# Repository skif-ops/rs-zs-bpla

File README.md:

# Дионея / РС ЗС-БПЛА — EVT-PRE-20

Эта ветка содержит инженерную базу одного управляемого предсерийного лота
`EVT-20`. Актуальная программа закупки — два отдельных набора по 20 станций и
один стендовый образец, всего 41 станция. Закупочная выдача имеет два явно
разделённых варианта: 21 станция (один EVT-20 плюс стендовая) и 41 станция
(два EVT-20 плюс стендовая). Расчёты для 4 и 10 станций сохранены для
сравнения, но не являются разрешением закупки.

## Зафиксированный baseline

- производственная единица управления: `EVT-20`, 20 изделий;
- программа: `2 × EVT-20 + 1 bench`, 41 станция;
- варианты закупки: `21 = EVT-20 + bench` и `41 = 2 × EVT-20 + bench`;
- резервы: два независимых EVT-20 пула; стендовый образец не создаёт третий;
- серийные номера: первый лот `DIO-EVT-001…020`, второй `DIO-EVT-021…040`,
  стендовый образец `DIO-EVT-B01`; индивидуальные travellers заполняются до
  начала сборки;
- собственная PCB станции, без отладочной платы WeAct в составе изделия;
- вычислительная платформа: `STM32U585VIT6Q`, `LQFP100_14x14`;
- четыре одинаковых микрофона, схема 3+1, база 120 мм, верхний микрофон +150 мм;
- LiFePO4 12.8 В / 40 А·ч и солнечная панель 80 Вт по точным MPN baseline;
- GSM/LTE через исходящее MQTT/TLS, резерв HTTPS/TLS, два nano-SIM в режиме
  Dual SIM Single Standby и только `public APN` в пилоте;
- LoRa `RU868` на каждом изделии; будущий `EU868` профиль в пилот не прошивается;
- BLE используется для локальной настройки, диагностики и безопасного обновления;
- корпус первого EVT-20 лота — вакуумное литьё; 3D-печать остаётся управляемым
  резервом, а ТПА — только комплектом исходных данных;
- сервер — «Мухоед» для Windows 11 и Ubuntu 24.04; Android ведётся отдельным треком.

## Текущий статус

Общий статус аппаратного выпуска: `BLOCKED / EVT NOT RUN`. Наличие документов и
успешные структурные проверки не являются завершённым аппаратным EVT.

| Область | Принято | Остаётся открытым |
|---|---|---|
| PCB-MAIN | 8L COMPLETE-105 Rev.B; `JLC08161H-3313`; 5969 route segments; 251 components; KiCad DRC 0 errors / 0 unconnected | selected-stack impedance/return-path review, POFV confirmation, Altium antenna-warning disposition, checkout DFM, Review B |
| PCB-PWR | `DIM-003` `18/18`; 90×60×1.6 mm; H1-H4 M3 NPTH; `JLC04161H-3313A`; 70/35 µm copper; ≥18 µm hole wall; расчётная силовая геометрия; точный ECO-002 применён, 14 принятых сегментов; application gate PASS | input-protection qualification, оставшаяся трассировка, rail-drop/load-step/fault/+70 °C evidence, DRC, CAM, checkout DFM, Review B |
| PCB-MIC | copper subgate и стандартный двухслойный/PCBA процесс; 9/9 engineering closures | first-panel bore/acoustic inspection, CAM comparison, общий Review B и physical EVT |
| Жгуты | 38 проводников; точные wire MPN; длины `275/440/330 mm` с 10% запасом; 16/16 engineering closures | first-off crimp height/pull, 100% continuity/polarity/cross-short/resistance, installed-route SI/thermal/cold/strain EVT |
| BOM | QG-1 PASS; technical QG-2 PASS; per-lot 4/10/20 и aggregate 41-station procurement plan | коммерческий заказ и hardware manufacturing release |
| Внешние ответы | бывшие wait gates закрыты `85/85` инженерным EVT baseline | factory e-mail не требуется; реальные checkout parser/DFM ошибки останавливают заказ и идут через ECO |

Закрытия в response-регистрах принадлежат проектной инженерии по решению
заказчика и не выдаются за ответы фабрик. Стандартные процессы приняты только для
тестовой EVT-программы; при переходе в серию повторяются supplier/site, tooling,
DFM и process qualification.

PCB-PWR `VBAT_RAW` routing 003 и `REV_GATE` routing 004 применены и прошли
точные application gates. Точный `PCB-PWR-BUCK-POWER-STAGE-ECO-002` теперь
применён к authoritative board; активная плата содержит 14 принятых сегментов,
ноль vias и ноль zones. Commit-bound application gate прошёл CI #692,
PCB-PWR Schematic #103 и PCB Native #357. Физический first-article +70 °C,
оставшаяся трассировка и все выпускные гейты открыты.

Серверная часть включает обновлённую обработку подтверждённого класса «лютый» в
трёх проверенных аудиосценариях «Мухоеда»; это программное изменение не закрывает
аппаратные гейты.

## Контроль выпуска

Каждый поставочный объект проходит два последовательных контроля:

1. `QG-1 Completeness` — наличие, версия, взаимные ссылки и контрольная сумма.
2. `QG-2 Technical` — ERC/DRC, сборка, тест, визуальная проверка или измерение.

Основные команды:

```bash
python tools/validate_evt_pre_20_bom_qg1.py
python tools/audit_evt_pre_20_bom_qg2.py --strict
python tools/audit_evt_engineering_manufacturing_baseline_rev_a.py
python tools/audit_evt_pre_20_hardware_release.py
python tools/kicad_native_gate.py
```

Gerber, прошивки, бинарники, корпуса и серверный релиз не считаются выпущенными,
пока их собственные гейты не имеют требуемые evidence. Hardware-only gate не
блокируется Android/server/обычным firmware, кроме явных аппаратных зависимостей.

## Навигация

- [`BRANCH_SCOPE.md`](BRANCH_SCOPE.md) — границы ветки и актуальный срез.
- [`config/EVT_PRE_20_BASELINE.yaml`](config/EVT_PRE_20_BASELINE.yaml) — машинно-читаемая конфигурация.
- [`docs/DELIVERABLE_REGISTER_EVT_PRE_20.csv`](docs/DELIVERABLE_REGISTER_EVT_PRE_20.csv) — реестр поставки и gates.
- [`docs/OPEN_INPUTS_FOR_FREEZE.csv`](docs/OPEN_INPUTS_FOR_FREEZE.csv) — входные данные, блокирующие финальный выпуск.
- [`docs/EVT_PRE_20_LONG_RANGE_ACOUSTIC_HEAD_TRADE_STUDY_REV_C.pdf`](docs/EVT_PRE_20_LONG_RANGE_ACOUSTIC_HEAD_TRADE_STUDY_REV_C.pdf) — актуальный двуязычный управляемый выпуск исследования дальнего акустического тракта: физика распространения, классы целей, сравнение микрофонов, рупоров, отражателей и резонаторов, план прототипа LR-1. Производственный baseline плат не изменён.
- [`hardware/EVT_PRE_20_ACOUSTIC_TRADE_STUDY_REV_C.xlsx`](hardware/EVT_PRE_20_ACOUSTIC_TRADE_STUDY_REV_C.xlsx) — сводная книга вариантов, целевых классов, расчёта потерь на 2 км, матрицы физических испытаний и источников. Машиночитаемые таблицы сохранены рядом в CSV.
- [`hardware/EVT_PRE_20_BOM_POLICY_REV_A.md`](hardware/EVT_PRE_20_BOM_POLICY_REV_A.md) — BOM и количества.
- [`hardware/EVT_PROGRAM_PROCUREMENT_VARIANTS_REV_A.csv`](hardware/EVT_PROGRAM_PROCUREMENT_VARIANTS_REV_A.csv) — реестр вариантов закупки 21 и 41.
- [`hardware/EVT_PROGRAM_1X20_PLUS_1_PROCUREMENT_REV_A.csv`](hardware/EVT_PROGRAM_1X20_PLUS_1_PROCUREMENT_REV_A.csv) — вариант на 21 станцию.
- [`hardware/EVT_PROGRAM_2X20_PLUS_1_PROCUREMENT_REV_A.csv`](hardware/EVT_PROGRAM_2X20_PLUS_1_PROCUREMENT_REV_A.csv) — полный план на 41 станцию.
- [`hardware/HARDWARE_PRODUCTION_RELEASE_GATE_REV_A.md`](hardware/HARDWARE_PRODUCTION_RELEASE_GATE_REV_A.md) — hardware release gate.
- [`manufacturing/README.md`](manufacturing/README.md) — маршрут сборки, traceability и EOL.
- [`tests/EVT_MASTER_PLAN.md`](tests/EVT_MASTER_PLAN.md) — последовательность EVT.
- [`android/README.md`](android/README.md) — отдельный Android-трек.

## Наследование

Ветка создана от `evt` commit `2ec1d6dc81e3a16b7c127f1bbfe03f3945a72c45`.
Поставочные материалы `evt-mb` сюда не переносятся. Общие проверенные изменения
могут отдельно продвигаться в `develop` и `main`. Макетная плата 70×90 мм и
WeAct STM32U585CIU6 не являются производственной документацией EVT-PRE-20.

## Финальный производственный комплект REV_D7

Финальная документальная выдача для закупки и производства EVT-PRE-20 находится в
[`releases/EVT_PRE_20_REV_D7`](releases/EVT_PRE_20_REV_D7/README.md). PCB-MAIN Rev.B
зафиксирована как восьмислойная. Фабричный архив содержит Altium/CAM для PCB-MAIN,
PCB-PWR и PCB-MIC без KiCad. Физические first article, EOL и EVT заполняются после
изготовления и не отмечены как выполненные заранее.

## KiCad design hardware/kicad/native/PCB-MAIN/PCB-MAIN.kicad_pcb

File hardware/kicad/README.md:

> **CURRENT PCB-MAIN SOURCE — REV.B (2026-10-16):** `native/PCB-MAIN/PCB-MAIN.kicad_pcb` is now PCB-MAIN COMPLETE-105 Rev.B with 8 copper layers. The former 6-layer native source is preserved under `retired/PCB-MAIN-6L-REV-A-2026-10-16/`. Rev.A 6-layer routing/stack sections below are historical.

# ZS-BPLA EVT-PRE-20 KiCad package

Status: `NATIVE SOURCE CONTROLLED / NOT FOR MANUFACTURE`
Configuration: `EVT-PRE-20 Rev.A`
Authoritative branch: `evt-pre-20`

This directory is the authoritative electrical-CAD source package for the EVT-PRE-20 custom-PCB build. The three native projects and their required hierarchical child sheets are present. It remains blocked from manufacturing until each provisional board is completed and the required ERC/DRC, CAM, DFM and independent reviews are complete.

## Frozen baseline used for capture

- MCU: `STM32U585VIT6Q`, LQFP100 14x14 mm. The earlier `STM32U585CIU6`/48-pin and `STM32U585ZIT6Q` references are superseded for EVT-PRE-20.
- Microphones: 4 x TDK/InvenSense `T5838`, identical MPN; same lot preferred.
- Acoustic geometry: 3+1, equilateral base 120 mm, upper microphone +150 mm over center.
- Cellular: Quectel `BG95-M3` candidate, two physical nano-SIM slots through external 2:1 SIM mux, Dual-SIM Single-Standby only.
- GNSS/PPS: independent u-blox `MAX-M10S` class receiver.
- LoRa: Ebyte `E22-900M22S` / SX1262 class, RU868 pilot profile on every station in the selected 4, 10 or 20-unit EVT lot.
- BLE commissioning/diagnostics/OTA coprocessor: Raytac `MDBT50Q-P1MV2` based on Nordic `nRF52840`, integrated PCB antenna. `ESP32-C3-MINI-1-N4` is superseded and forbidden in active Rev.A BOM/capture.
- BLE requirements: BLE 2M/1M/Coded Long Range, authenticated commissioning, signed OTA, local diagnostics; Wi-Fi is not required.
- Local storage: W25Q512-class 64 MB NOR plus industrial microSD.
- Power source: 12.8 V LiFePO4 40-60 Ah, external 10 A LiFePO4 MPPT, 60-80 W solar panel.
- MPPT function is external. Do not reintroduce the older BQ24650/CN3791 charger topology into EVT-PRE-20 PCB-MAIN or PCB-PWR.

## PCB set

1. `PCB-MAIN`: MCU, BG95, dual SIM, MAX-M10S, LoRa module, nRF52840 BLE module, NOR, microSD, sensors, USB service, SWD and test points.
2. `PCB-MIC`: one T5838 microphone leaf; four identical boards per station.
3. `PCB-PWR`: protected battery interface and DC/DC rails for 3.8 V modem, 3.3 V digital/AON and 1.8 V microphone domains. External MPPT remains a separate assembly.

PCB-PWR `C1-C21`, `R1-R15`, `NT1-NT3` and `TP1-TP10` are bound from
`hardware/PCB_PWR_PASSIVE_AUTHORITY_REV_A.csv`. This is a capture/placement input,
not a manufacturing release; its electrical, package, fixture and environmental
blockers remain explicit in the authority.

PCB-PWR now uses a human-readable five-page native hierarchy: one system overview
plus four functional child sheets for input protection/current monitoring, 3V8,
3V3 and 1V8/harness interfaces. The controlled materializer gives every connected
pin an explicit wire stub and the independent audit proves exact pad/net
equivalence to the native PCB. The C20/C21 local-CIN_HF ECO supersedes prior
KiCad 9 ERC/PDF and human decisions for the active source; fresh commit-bound
evidence and independent human acceptance remain open.

PCB-PWR currently contains a native, unrouted placement canvas with 62 electrical
footprints plus four board-only mounting holes. `DIM-003` is accepted `18/18`
for the EVT batch: the `90 x 60 x 1.6 mm` basis, round H1-H4 NPTH pattern,
connector/fixture service volumes and conservative STEP envelope are controlled.
Routing and copper zones remain absent; serial enclosure revalidation is mandatory.
`hardware/PCB_PWR_CAPTURE_STATUS_REV_A.json` is the machine-readable release
interlock for this state.

The bounded `DIM-003` authority is controlled by
`hardware/reviews/PCB_PWR_DIM_003_REQUEST_REV_A.json`; all 18 response rows are
accepted for EVT. It freezes the EVT outline, mounting, J1/J2, DFT,
assembled-height, enclosure/thermal, harness-datum and frozen-STEP inputs without
authorizing serial mechanics or manufacture.

The bounded fitted-body clearance repack passes a strict independent subgate:
all 44 simultaneously fitted footprints have controlled courtyards, the required
minimum gap is `0.20 mm`, the observed minimum is `0.22 mm`, and conflicts are
zero. This result excludes DNP/PCB-feature service checks and does not approve
the serial enclosure and exact component 3D fit; EVT connector mating/bend
volumes, mounting, DFT fixture access and assembled envelope are accepted.
Routing and Review B remain open.

`hardware/PCB_PWR_ROUTING_AUTHORITY_REV_A.csv` classifies all 31 native nets as a
pre-route input, including high-current paths, three controlled net-tie returns,
switch/bootstrap loops, Kelvin sense, feedback and I2C. The separate
`PCB_PWR_JLC04161H_3313_EVT_ROUTING_BASIS_REV_A.json` plus the 31-row
`PCB_PWR_EVT_ROUTE_RULES_REV_A.csv` now permit a bounded engineering routing
candidate using a conservative 35 µm screen. `DIM-003` is accepted for EVT;
final copper/plating, via-current capacity, fault energy, physical thermal
evidence, routing completion and manufacture remain open.

## Logical sheet plan

1. `01_POWER` - protected input and regulated rails; no integrated solar MPPT.
2. `02_MCU` - STM32U585VIT6Q, clocks, reset, SWD, decoupling, boot straps.
3. `03_AUDIO` - four PDM channels, common clock fanout/interface, microphone connectors.
4. `04_GNSS` - MAX-M10S, TIMEPULSE/PPS, RF connector/bias, backup supply.
5. `05_CELLULAR` - BG95-M3, 3.8 V transient decoupling, 1.8 V logic translation, dual nano-SIM mux and ESD.
6. `06_LORA` - E22-900M22S/SX1262 interface, RF connector/matching/ESD.
7. `07_BLE` - Raytac MDBT50Q-P1MV2 / nRF52840 service, commissioning and OTA coprocessor with SWD/UART recovery access and antenna keepout.
8. `08_STORAGE_SENSORS` - W25Q512, industrial microSD, LIS2DW12, temperature and current/voltage monitoring.
9. `09_CONNECTORS_TEST` - PCB-PWR, MIC1..MIC4, USB-C service, SWD, production test fixture and revision straps.

## Required CAD gates before Gerber release

- Pre-schematic PCB-MAIN authorities `MAIN-AUTH-001…011` are closed; the 110 x 75 mm outline, connector/module anchors, RF/keepout regions and 31 production pogo-pad coordinates are frozen by `hardware/PCB_MAIN_MECHANICAL_PLACEMENT_AUTHORITY_REV_A.csv`.
- Treat that frozen PCB-MAIN placement as a capture baseline, not a released
  placement: the accepted limited mechanical ECO-001/002 chain clears the
  conflicts that were inside MAIN-AUTH-011, including the bounded J_PWR/J6/H1
  geometry. The controlled 225-reference functional repack and
  explicit generic-passive courtyards now pass the independent strict 2D audit:
  227/227 fitted assembly footprints have courtyards and all component,
  mounting-exclusion and U.FL tool-zone conflict sets are empty. Routing,
  KiCad DRC, 3D/service review and Review B remain required.
- Use `hardware/PCB_MAIN_ROUTING_AUTHORITY_REV_A.csv` as the controlled pre-route
  input. It explicitly classifies all 186 native nets and preserves separate
  `GND_MODEM`, `GND_DIGITAL` and `GND_MIC` references. Its PASS is constraint
  coverage plus accepted EVT numeric geometry, not complete routing. The active
  board has 1023 trace items and eight copper zones; final SI, remaining routing,
  DRC and manufacturing evidence remain open.
- `hardware/reviews/PCB_MAIN_STACKUP_IMPEDANCE_REQUEST_REV_A.json` is a retained
  historical checklist. Its 22/22 rows are engineering-baseline closures;
  `JLC06161H-3313` and the controlled 50/90-ohm geometry are accepted for EVT.
- Use `hardware/reviews/PCB_MAIN_ASSEMBLER_DFM_STENCIL_REQUEST_REV_A.json` and
  its 14/14 engineering-closure register for the bounded `U2/U25/U26/U9`
  standard-process review. Controlled paste export still waits for native DRC
  and CAM; first article and Review B remain mandatory.
- Use `hardware/PCB_PWR_ROUTING_AUTHORITY_REV_A.csv` as the 31-net PCB-PWR
  pre-route input and `hardware/PCB_PWR_EVT_ROUTE_RULES_REV_A.csv` as the bounded
  numeric EVT overlay. Preserve `DIM-003`; route an engineering candidate only
  against the 35 µm lower-bound rules and accepted EVT ordering profile
  `JLC04161H-3313A`, 1.6 mm, outer 2 oz / inner 1 oz. The active board has only
  exactly 14 accepted trace items after hash-bound power-stage ECO-002 application
  and zero vias/zones; the ECO-002 commit-bound application gate passed at CI #692,
  PCB-PWR Schematic #103 and PCB Native #357.
  Fabrication still requires remaining routing, current/fault and physical +70 °C
  thermal evidence.
- `hardware/reviews/PCB_PWR_STACKUP_COPPER_REQUEST_REV_A.json` is retained for
  traceability. Its 24/24 rows are engineering-baseline closures and no factory
  reply is required. Any checkout DFM deviation must be resolved by ECO.
- Preserve the strict PCB-PWR fitted-body clearance PASS and its six-reference
  coordinate delta; repeat the audit after any placement or footprint change.
- Freeze CubeMX pin/peripheral assignment for STM32U585VIT6Q; no unresolved AF conflicts.
- Complete and review MAIN/PWR routing; keep all native
  `.kicad_sch/.kicad_pcb/.kicad_pro` sources under CI control.
- Datasheet/reference-design review for STM32U585, T5838, BG95, MAX-M10S, E22/SX1262, nRF52840/Raytac module and all power ICs.
- ERC: zero unexplained errors.
- DRC: zero blocker/critical violations.
- Review modem burst current, brownout and decoupling at 3.8 V.
- Review PDM 1.8 V level compatibility, clock fanout and channel-to-channel skew.
- Review dual-SIM powered-off isolation, signal integrity and low-capacitance ESD.
- RF review for cellular/GNSS/LoRa 50-ohm paths, BLE 2.4 GHz antenna keepout, grounding and coexistence.
- Validate BLE range/RSSI/OTA throughput in the final vacuum-cast housing and the full-lot 3D fallback housing.
- USB differential pair and ESD review.
- Power-current/thermal review for PCB-PWR including fault cases.
- DFT review: SWD, reset, rails, production UART and fixture-accessible test points.
- Generate and inspect Gerber, Excellon, IPC-356, pick-and-place, BOM/AVL, assembly drawings, fabrication notes and STEP.
- Independent Review A: schematic/net/pin/BOM check against source requirements.
- Independent Review B: PCB/CAM/assembly/DFM check against released source.

## Manufacturing prohibition

Do not manufacture or assemble EVT-PRE-20 PCB from the CSV sheets, component lists, current placeholder `.kicad_pro`, or any Gerber generated before both independent reviews pass. The release flag may change to `FOR_MANUFACTURE` only when the production gate and SHA-256 manifest are complete.

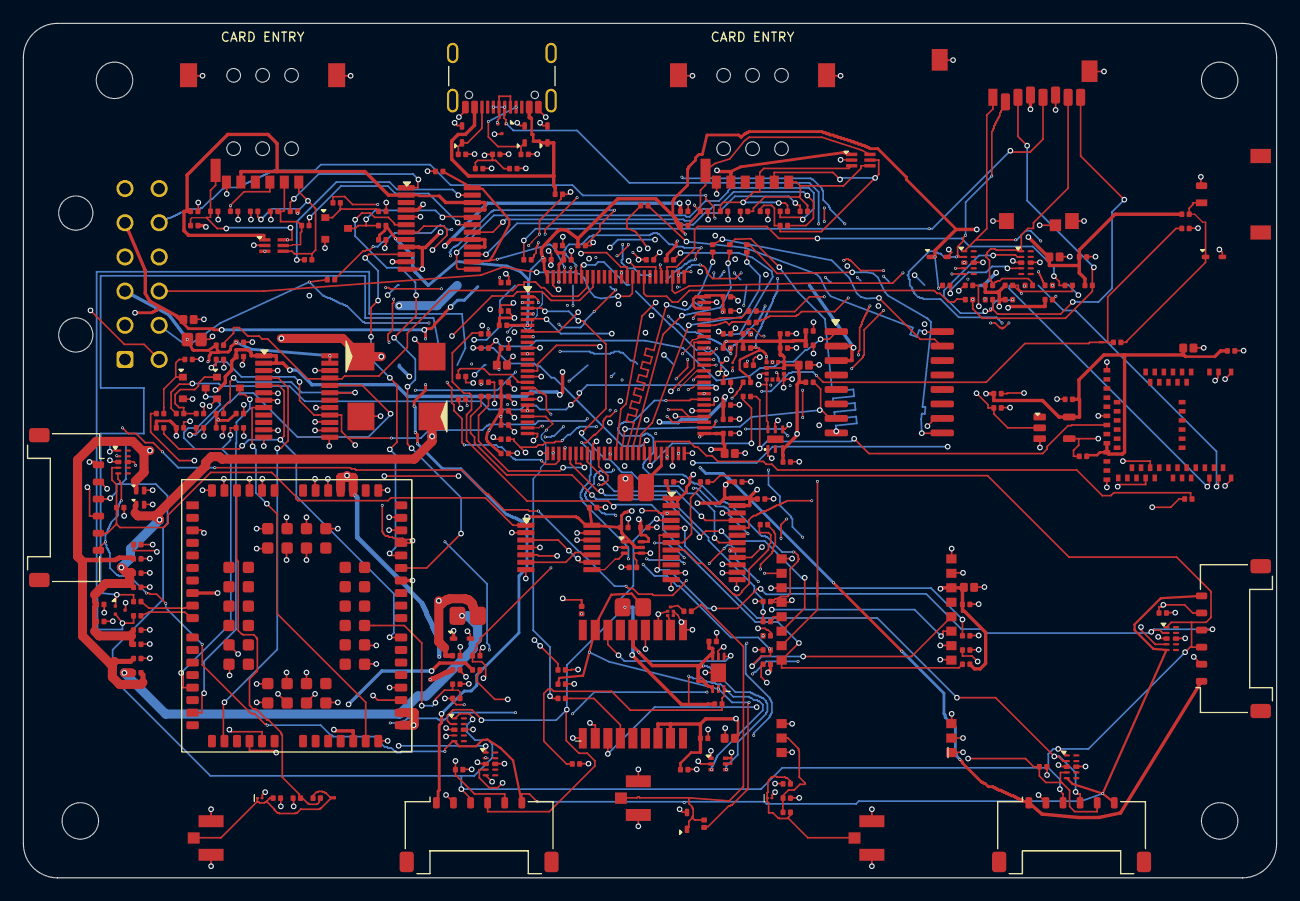
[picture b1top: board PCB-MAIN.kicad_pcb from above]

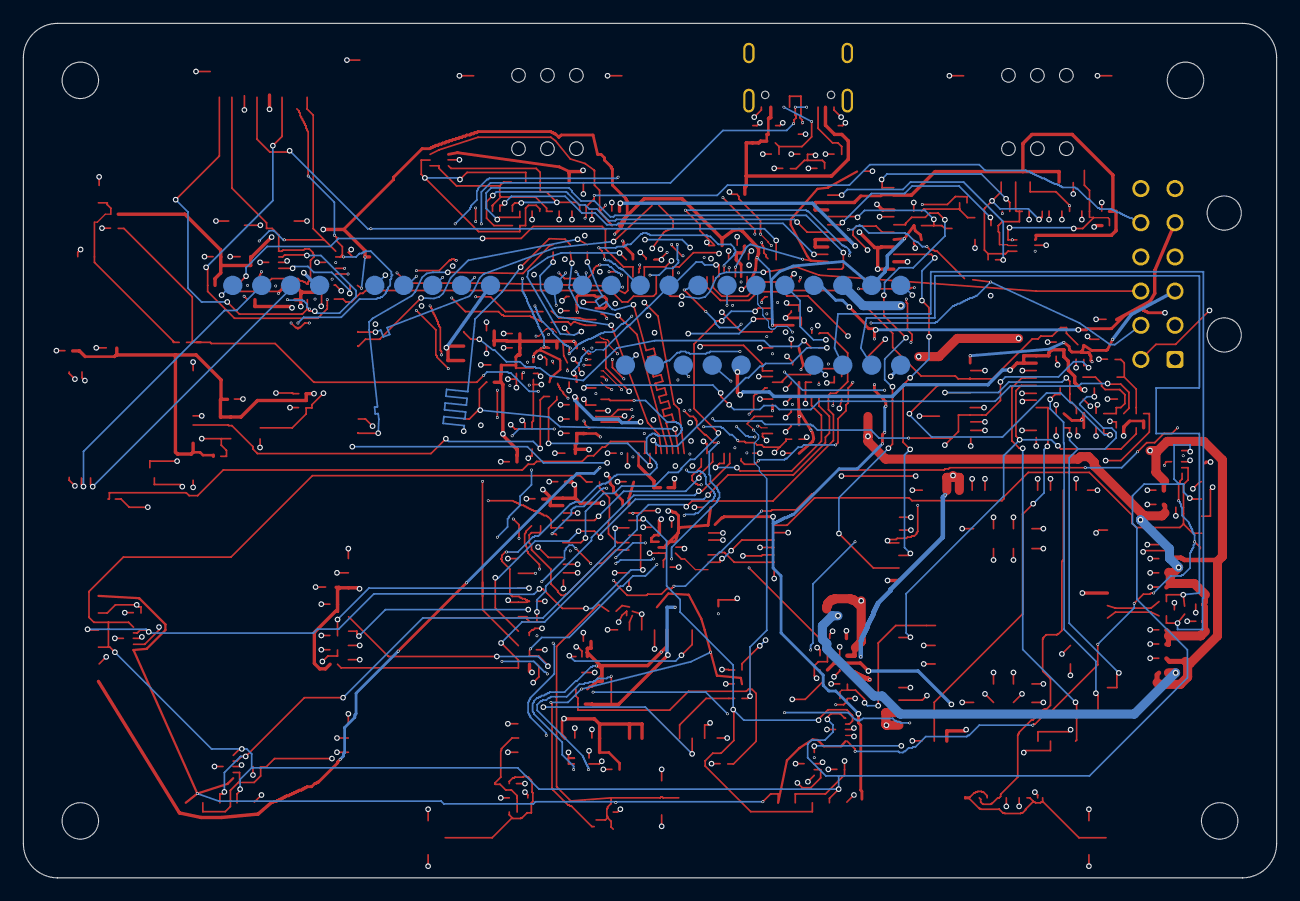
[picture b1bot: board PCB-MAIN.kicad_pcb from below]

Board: 8 copper layers, 110.0 x 75.0 mm, 251 parts (5 on the bottom side), 185 nets.

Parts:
C1, C2, C3, C4, C5, C7, C8, C10, C12, C16, C17, C18, C21, C23, C25, C26, C27, C28, C29, C30, C31, C32, C33, C34, C35, C45, C49, C50, C51, C60, C62, C65, C66, C68, C71, C73, C74: GRM155R71E104KE14D
C6, C13, C20, C24, C61, C67, C72, C75: GRM188R61A106KE69D
C9, C11, C22: GRM155R61C105KA12D
C14, C15: GRM155R61A225KE15D
C19: GRM21BR61A226ME44L
C36, C44: T520D107M006ATE015; KEMET_T52X_D_7343-31_DensityB
C37: GRM155R71E224KE14D
C38: GRM155R71E473KA01D
C39: GRM1555C1H151JA01D
C40: GRM1555C1H101JA01D
C41: GRM1555C1H680JA01D
C42, C46, C54, C55, C56, C57, C58, C59: GRM1555C1H330JA01D
C43, C47, C69, C70, C79, C80: GRM1555C1H100JA01D
C48, C52, C53, C76, C78: GRM155R71E103KA01D
C63: GRM155R71C103KA01D
C64: GRM1555C1E470JA01D
C77: GRM155R72A472KA01D
D1, D2: PESD5V0S1UL; Nexperia_PESD5V0S1UL_SOD882
D3, D5: PESD5V0C1BSF; PESD5V0C1BSF_SOD962-2
D4, D6, D7, D8, D9, D10, D11: TPD1E05U06DYAR; TI_DYA0002A_SOD523
FB1: BLM31KN601SN1L
FL1: ABSES5AF-L100KM; Abracon_ABSES5AF_1109-5
H1, H2, H3, H4: M3_NPTH
J6, J7: 2336582-1; TE_2336582-1_NanoSIM
J8, J9, J10: U.FL-R-SMT-1(60); Hirose_U.FL-R-SMT-1
J11: USB4105-GF-A-120; USB_C_Receptacle_GCT_USB4105-xx-A_16P_TopMnt_Horizontal
J12: MEM2052-00-195-00-A; GCT_MEM2052-00-195-00-A
J13: 504050-0291; Molex_504050-0291_PicoLock-2
J_MIC1, J_MIC2, J_MIC3, J_MIC4: 504050-0691; Molex_Pico-Lock_504050-0691_1x06-1MP_P1.50mm_Horizontal
J_PWR1: 43045-1202; Molex_43045-1202_MicroFit-12_RA
L1: LQH32PN2R2NN0L
L2: LQW15AN27NJ00D
Q1, Q2, Q3: MMBT3904,215; Nexperia_MMBT3904_SOT23
Q4: Si1016X-T1-GE3; Vishay_Si1016X_SC-89
R1, R7, R28, R30, R31, R46, R48, R49, R67, R68, R76, R78, R85, R86, R87, R88, R89, R90, R99: ERJ-2RKF1002X
R2, R3, R4, R5, R6, R19, R20, R21, R22, R23, R29, R32, R33, R34, R35, R45, R47, R63, R64, R65, R66, R77, R96: ERJ-2RKF1003X
R8, R9, R10, R11, R12, R15, R16, R17, R18, R36, R37, R56, R57, R58, R69, R70, R71, R72, R74, R75, R79, R80, R81, R82, R83, R84, R91, R92, R101: ERJ-2RKF22R0X
R13, R14: ERJ-2RKF2201X
R24, R26: ERJ-2RKF4701X
R25, R27, R44: ERJ-2RKF4702X
R38, R41, R95, R100, R102: ERJ-2RKF1001X
R39, R40, R42, R43, R50, R51, R52, R53, R54, R55, R73, R98, R103: ERJ-2GE0R00X
R59: ERJ-2GEJ561X
R60, R61: ERJ-2GEJ104X
R62: ERJ-8GEYJ100V
R93, R94: ERJ-2RKF5101X
R97: ERJ-2RKF1004X
TP_BLE_SWD1: TEST_PADS
TP_CELL_DBG1: TEST_PADS
TP_CELL_USB1: TEST_PADS
TP_EOL1: TEST_PADS
TP_MCU_SWD1: TEST_PADS
U1: STM32U585VIT6Q; ST_STM32U585_LQFP100_1L
U2: W25Q512JVFIQ; Winbond_W25Q512JV_PackageF_IPC_Candidate
U3: LIS2DW12TR; ST_LIS2DW12_LGA-12L
U4: STTS22HTR; STTS22H_UDFN-6L
U5: LT6000IDCB#TRMPBF; LT6000_DCB-7
U6: SN74LVC1G07DBVR; TI_DBV0005A_SOT23-5
U7, U16: SN74AXC8T245PWR; TI_PW0024A_TSSOP24
U8: BG95-M3; Quectel_BG95-M3_LGA-102
U9: MAX-M10S-00B; u-blox_MAX-M10S_LCC-18
U10: E22-900M22S; Ebyte_E22-M22S_Castellated-22
U11: MDBT50Q-P1MV2; Raytac_MDBT50Q-P1MV2
U13: TS3A27518EPWR; TI_PW0024A_TSSOP24
U14, U15: ESDALC6V1-5P6; ST_ESDALC6V1-5P6_SOT666
U17: SN74LVC32APWR; TI_PW0014A_TSSOP14
U18: SN74AXC1T45DRLR; TI_DRL0006A_SOT6
U19, U20, U21, U22, U23, U24, U27: TPD4E05U06DQAR; TI_DQA0010A_USON10
U25, U26: TPD2EUSB30DRTR; TI_DRT0003A_IPC_Candidate
X1: SiT1552AI-JE-DCC-32.768D; SiT1552_JE_CSP-4

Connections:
1V8_MIC: C20.1, C27.1, C30.1, C31.1, J_MIC1.1, J_MIC2.1, J_MIC3.1, J_MIC4.1, J_PWR1.5, TP_EOL1.4, U7.1, U7.2, U17.14, U18.1, U18.5
3V3_DIGITAL: C1.1, C2.1, C3.1, C4.1, C5.1, C6.1, C7.1, C8.1, C9.1, C10.1, C11.1, C12.1, C13.1, C19.1, C21.1, C22.1, C23.1, C24.1, C25.1, C26.1, C28.1, C29.1, C32.1, C34.1, C35.1, C49.1, C60.1, C61.1, C62.1, C66.1, C67.1, C71.1, C72.1, C73.1, C74.1, C75.1, D11.1, J12.4, J_PWR1.3, R1.1, R4.1, R6.1, R7.1, R13.1, R14.1, R28.1, R32.1, R33.1, R44.1, R48.1, R49.1, R67.1, R68.1, R76.1, R78.1, R85.1, R86.1, R87.1, R88.1, R89.1, R90.1, R99.1, TP_BLE_SWD1.1, TP_EOL1.2, TP_MCU_SWD1.1, U1.6, U1.11, U1.20, U1.21, U1.27, U1.47, U1.51, U1.73, U1.75, U1.100, U2.2, U2.3, U3.2, U3.9, U3.10, U4.3, U6.5, U7.23, U7.24, U9.7, U9.8, U10.9, U11.28, U11.30, U13.8, U16.23, U16.24, U18.6, X1.3
3V8_MODEM: FB1.1, J_PWR1.1, R42.1, TP_EOL1.3
3V8_MODEM_BB: C36.1, C37.1, C38.1, C39.1, C40.1, C41.1, C42.1, C43.1, D1.1, FB1.2, U8.32, U8.33
3V8_MODEM_RF: C44.1, C45.1, C46.1, C47.1, D2.1, R42.2, U8.52, U8.53
AAD_CFG: U1.77, U7.16
AAD_CFG_1V8_FANOUT: J_MIC1.6, J_MIC2.6, J_MIC3.6, J_MIC4.6, R18.2, U19.5, U20.5, U21.5, U22.5
AAD_CFG_1V8_U7: R18.1, U7.8
ACCEL_INT: U1.63, U3.12
BLE_DFU_REQ: R76.2, U1.34, U11.39
BLE_EN: R77.1, U1.5, U6.2
BLE_RX_U1: R74.2, U1.45
BLE_RX_U11: R74.1, U11.22
BLE_TX_U1: R75.1, U1.44
BLE_TX_U11: R75.2, U11.24
BOOT0: R2.1, TP_EOL1.9, U1.94
CELL_DBG_RXD_TP: R37.1, TP_CELL_DBG1.3, U27.2
CELL_DBG_RXD_U8: R37.2, U8.22
CELL_DBG_TXD_TP: R36.2, TP_CELL_DBG1.2, U27.1
CELL_DBG_TXD_U8: R36.1, U8.23
CELL_DBG_VREF_TP: R41.2, U27.4
CELL_DTR_U16: R29.1, U1.61, U16.16
CELL_PWRKEY_CMD: R24.1, U1.58
CELL_RESET_N_CMD: R26.1, U1.59
CELL_RF: C79.1, R43.1, U8.60
CELL_RF_ANT: C80.1, D3.1, J8.1, R43.2
CELL_RI_U16: R33.2, U1.62, U16.19
CELL_RX_U16: R32.2, U1.93, U16.21
CELL_STATUS_U16: R34.1, U1.60, U16.20
CELL_TX_U16: R28.2, U1.92, U16.17
CELL_USB_BOOT_1V8: R35.1, R38.2, U8.75
CELL_USB_BOOT_TP: R38.1, TP_CELL_DBG1.4, U27.5
CELL_USB_DM_TP: R40.2, TP_CELL_USB1.3, U26.2
CELL_USB_DM_U8: R40.1, U8.10
CELL_USB_DP_TP: R39.2, TP_CELL_USB1.2, U26.1
CELL_USB_DP_U8: R39.1, U8.9
CELL_USB_VBUS: D10.1, TP_CELL_USB1.1, U8.8
CELL_USIM_CLK_1V8: U8.46, U13.7
CELL_USIM_DATA_1V8: U8.45, U13.10
CELL_USIM_RST_1V8: U8.44, U13.6
CELL_USIM_VDD_1V8: U8.43, U13.4, U13.9, U13.12
EN_AUX: J_PWR1.10, U1.86
EN_MODEM: J_PWR1.9, U1.85
FAULT: J_PWR1.8, R103.1, TP_EOL1.8
GND_DIGITAL: C1.2, C2.2, C3.2, C4.2, C5.2, C6.2, C7.2, C8.2, C9.2, C10.2, C11.2, C12.2, C13.2, C14.2, C15.2, C16.2, C17.2, C18.2, C19.2, C21.2, C22.2, C23.2, C24.2, C25.2, C26.2, C27.2, C28.2, C29.2, C31.2, C32.2, C60.2, C61.2, C62.2, C63.2, C65.2, C66.2, C67.2, C68.2, C69.2, C70.2, C71.2, C72.2, C73.2, C74.2, C75.2, C76.2, C77.2, C78.2, D4.2, D5.2, D6.2, D7.2, D8.2, D9.2, D11.2, FL1.B, FL1.D, FL1.E, J9.SHIELD, J10.SHIELD, J11.A1, J11.A12, J11.B1, J11.B12, J12.6, J12.SHIELD, J13.2, J_PWR1.4, Q4.1, R2.2, R3.2, R5.2, R23.2, R60.2, R63.2, R64.2, R65.2, R66.2, R77.2, R93.2, R94.2, R96.2, R97.2, R98.2, TP_BLE_SWD1.4, TP_EOL1.1, TP_MCU_SWD1.5, U1.10, U1.19, U1.26, U1.48, U1.50, U1.74, U1.99, U2.10, U3.3, U3.6, U3.7, U3.8, U4.4, U4.5, U5.5, U5.EP, U6.3, U7.11, U7.12, U7.13, U7.14, U7.15, U7.22, U9.1, U9.10, U9.12, U10.1, U10.2, U10.3, U10.4, U10.5, U10.10, U10.11, U10.12, U10.20, U10.22, U11.1, U11.2, U11.15, U11.33, U11.55, U18.2, U23.3, U23.8, U24.3, U24.8, U25.3, X1.1, X1.4
GND_MIC: C20.2, C30.2, J_MIC1.2, J_MIC2.2, J_MIC3.2, J_MIC4.2, J_PWR1.6, R19.2, R20.2, R21.2, R22.2, U17.7, U17.12, U17.13, U19.3, U19.8, U20.3, U20.8, U21.3, U21.8, U22.3, U22.8
GND_MODEM: C33.2, C34.2, C35.2, C36.2, C37.2, C38.2, C39.2, C40.2, C41.2, C42.2, C43.2, C44.2, C45.2, C46.2, C47.2, C48.2, C49.2, C50.2, C51.2, C52.2, C53.2, C54.2, C55.2, C56.2, C57.2, C58.2, C59.2, C79.2, C80.2, D1.2, D2.2, D3.2, D10.2, J6.4, J6.SHIELD, J7.4, J7.SHIELD, J8.SHIELD, J_PWR1.2, Q1.2, Q2.2, Q3.2, R25.2, R27.2, R29.2, R34.2, R35.2, R45.2, R47.2, TP_CELL_DBG1.5, TP_CELL_USB1.4, U8.3, U8.31, U8.47, U8.48, U8.50, U8.54, U8.55, U8.58, U8.59, U8.61, U8.62, U8.67, U8.68, U8.69, U8.70, U8.71, U8.72, U8.73, U8.74, U8.79, U8.80, U8.81, U8.82, U8.89, U8.90, U8.91, U8.100, U8.101, U8.102, U13.5, U14.2, U15.2, U16.6, U16.11, U16.12, U16.13, U16.14, U16.15, U16.22, U26.3, U27.3, U27.8
GNSS_ANT_BIAS_RAW: C65.1, Q4.4, R61.1, U5.3, U5.4, U9.14
GNSS_ANT_DETECT: U5.6, U9.16
GNSS_ANT_DIV: R59.2, R60.1, U5.1
GNSS_ANT_GATE: Q4.5, Q4.6, R61.2
GNSS_ANT_OFF_N: Q4.2, U9.13
GNSS_ANT_SHORT_N: C63.1, L2.1, R62.2, U5.2, U9.17
GNSS_ANT_SWITCHED: Q4.3, R59.1, R62.1
GNSS_PPS_U1: R58.2, U1.22
GNSS_PPS_U9: R58.1, U9.4
GNSS_RF_ANT_BIASED: C64.1, D4.1, J9.1, L2.2
GNSS_RF_DC_BLOCK: C64.2, FL1.C
GNSS_RF_FILTERED: FL1.A, U9.11
GNSS_RX_U1: R56.2, U1.25
GNSS_RX_U9: R56.1, U9.2
GNSS_TX_U1: R57.1, U1.24
GNSS_TX_U9: R57.2, U9.3
HW_REV0: R3.1, R4.2
HW_REV1: R5.1, R6.2
I2C2_SCL_BUS: J_PWR1.11, R13.2, R15.2, TP_EOL1.12, U3.1, U4.1
I2C2_SCL_U1: R15.1, U1.52
I2C2_SDA_BUS: J_PWR1.12, R14.2, R16.2, TP_EOL1.13, U3.4, U4.6
I2C2_SDA_U1: R16.1, U1.53
LORA_BUSY: R66.1, U1.56, U10.14
LORA_DIO1: R65.1, U1.17, U10.13
LORA_MISO_U1: R72.2, U1.30
LORA_MISO_U10: R72.1, U10.16
LORA_MOSI_U1: R71.1, U1.31
LORA_MOSI_U10: R71.2, U10.17
LORA_NSS_U1: R69.1, U1.28
LORA_NSS_U10: R68.2, R69.2, U10.19
LORA_RESET_N: C68.1, R67.2, U1.57, U10.15
LORA_RF_ANT: C70.1, D5.1, J10.1, R73.2
LORA_RF_MODULE: C69.1, R73.1, U10.21
LORA_RXEN: R64.1, U1.55, U10.6
LORA_SCK_U1: R70.1, U1.29
LORA_SCK_U10: R70.2, U10.18
LORA_TXEN: R63.1, U1.54, U10.7
LSE_IN: U1.8, X1.2
MIC_WAKE: R23.1, U1.67, U18.4
MIC_WAKE1: J_MIC1.5, R19.1, U17.1, U19.4
MIC_WAKE2: J_MIC2.5, R20.1, U17.2, U20.4
MIC_WAKE3: J_MIC3.5, R21.1, U17.4, U21.4
MIC_WAKE4: J_MIC4.5, R22.1, U17.5, U22.4
MIC_WAKE12_OR_1V8: U17.3, U17.9
MIC_WAKE34_OR_1V8: U17.6, U17.10
MIC_WAKE_OR_1V8: U17.8, U18.3
NOR_CLK_U1: R8.1, U1.38
NOR_CLK_U2: R8.2, U2.16
NOR_IO0_U1: R9.1, U1.40
NOR_IO0_U2: R9.2, U2.15
NOR_IO1_U1: R10.1, U1.41
NOR_IO1_U2: R10.2, U2.8
NOR_IO2_U1: R11.1, U1.42
NOR_IO2_U2: R11.2, U2.9
NOR_IO3_U1: R12.1, U1.43
NOR_IO3_U2: R12.2, U2.1
NOR_NCS_U2: R7.2, U1.39, U2.7
NRF_RESET_N: R78.2, U6.4, U11.40
NRF_SWCLK: TP_BLE_SWD1.3, U11.53
NRF_SWDIO: TP_BLE_SWD1.2, U11.51
NRST: C18.1, R1.2, TP_MCU_SWD1.4, U1.14
PDM_CLK: U1.37, U7.17
PDM_CLK_1V8_FANOUT: J_MIC1.3, J_MIC2.3, J_MIC3.3, J_MIC4.3, R17.2, U19.1, U20.1, U21.1, U22.1
PDM_CLK_1V8_U7: R17.1, U7.7
PDM_DATA1: U1.33, U7.21
PDM_DATA1_1V8: J_MIC1.4, U7.3, U19.2
PDM_DATA2: U1.87, U7.20
PDM_DATA2_1V8: J_MIC2.4, U7.4, U20.2
PDM_DATA3: U1.35, U7.19
PDM_DATA3_1V8: J_MIC3.4, U7.5, U21.2
PDM_DATA4: U1.3, U7.18
PDM_DATA4_1V8: J_MIC4.4, U7.6, U22.2
PWR_FAULT: R103.2, U1.82
PWR_GOOD: J_PWR1.7, TP_EOL1.7, U1.81
Q1_BASE: Q1.1, R24.2, R25.1
Q2_BASE: Q2.1, R26.2, R27.1
Q3_BASE: Q3.1, R46.2, R47.1
REV_STRAP0: TP_EOL1.10, U1.95
REV_STRAP1: TP_EOL1.11, U1.96
SD_CK_CARD: J12.5, R79.2, U23.5
SD_CK_U1: R79.1, U1.80
SD_CMD_CARD: J12.3, R80.2, R85.2, U23.4
SD_CMD_U1: R80.1, U1.83
SD_D0_CARD: J12.7, R81.2, R86.2, U24.1
SD_D0_U1: R81.1, U1.65
SD_D1_CARD: J12.8, R82.2, R87.2, U24.2
SD_D1_U1: R82.1, U1.66
SD_D2_CARD: J12.1, R83.2, R88.2, U23.1
SD_D2_U1: R83.1, U1.78
SD_D3_CARD: J12.2, R84.2, R89.2, U23.2
SD_D3_U1: R84.1, U1.79
SD_DET: C76.1, J12.CD, R90.2, U1.7, U24.4
SIM1_CLK_CONN: C55.1, J6.3, R51.2, U14.4
SIM1_CLK_MUX: R51.1, U13.23
SIM1_DATA_CONN: C56.1, J6.6, R52.2, U14.5
SIM1_DATA_MUX: R52.1, U13.19
SIM1_DET: C52.1, J6.7, R48.2, U1.2, U14.6
SIM1_RST_CONN: C54.1, J6.2, R50.2, U14.3
SIM1_RST_MUX: R50.1, U13.1
SIM1_VDD_CONN: C50.1, J6.1, U13.2, U13.21, U13.22, U14.1
SIM2_CLK_CONN: C58.1, J7.3, R54.2, U15.4
SIM2_CLK_MUX: R54.1, U13.15
SIM2_DATA_CONN: C59.1, J7.6, R55.2, U15.5
SIM2_DATA_MUX: R55.1, U13.18
SIM2_DET: C53.1, J7.7, R49.2, U1.4, U15.6
SIM2_RST_CONN: C57.1, J7.2, R53.2, U15.3
SIM2_RST_MUX: R53.1, U13.13
SIM2_VDD_CONN: C51.1, J7.1, U13.11, U13.16, U13.17, U15.1
SIM_MUX_EN: R46.1, U1.1
SIM_MUX_SEL: R45.1, U1.97, U13.14, U13.24
SMPS_SW: L1.1, U1.46
SWCLK: TP_MCU_SWD1.3, U1.76
SWDIO: TP_MCU_SWD1.2, U1.72
TAMPER_IN_CONN: D9.1, J13.1, R99.2, R100.1
TAMPER_IN_U1: C78.1, R100.2, U1.64
TEST_UART_RX_TP: R102.1, TP_EOL1.6
TEST_UART_RX_U1: R102.2, U1.15
TEST_UART_TX_TP: R101.2, TP_EOL1.5
TEST_UART_TX_U1: R101.1, U1.16
U8_MAIN_DTR_1V8: U8.30, U16.8
U8_MAIN_RI_1V8: R31.2, U8.39, U16.5
U8_MAIN_RXD_1V8: U8.34, U16.7
U8_MAIN_TXD_1V8: R30.2, U8.35, U16.3
U8_PWRKEY_N: C48.1, Q1.3, U8.15
U8_RESET_N: Q2.3, U8.17
U8_STATUS_1V8: U8.20, U16.4
U8_VDD_EXT_1V8: C33.1, R30.1, R31.1, R41.1, TP_CELL_DBG1.1, U8.29, U16.1, U16.2
U13_EN_N: Q3.3, R44.2, U13.20
USB_CC1: D7.1, J11.A5, R93.1
USB_CC2: D8.1, J11.B5, R94.1
USB_DM_CONN: J11.A7, J11.B7, R92.2, U25.2
USB_DM_U1: R92.1, U1.70
USB_DP_CONN: J11.A6, J11.B6, R91.2, U25.1
USB_DP_U1: R91.1, U1.71
USB_SHIELD: C77.1, J11.SHIELD, R97.1, R98.1
USB_VBUS_CONN: D6.1, J11.A4, J11.A9, J11.B4, J11.B9, R95.1
USB_VBUS_SENSE: R95.2, R96.1, U1.68
VCORE_1V1: C14.1, C15.1, C16.1, C17.1, L1.2, U1.49, U1.98

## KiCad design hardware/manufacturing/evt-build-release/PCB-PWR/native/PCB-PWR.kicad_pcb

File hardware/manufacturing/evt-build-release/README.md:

# EVT-PRE-20 current-source EVT build release - 2026-10-16

Status: **EVT BUILD AUTHORIZED / CUSTOMER CHECKOUT REQUIRED.**

PCB-MAIN is `COMPLETE-105 Rev.B`, eight copper layers, preferred order stack `JLC08161H-3313`, 1.6 mm, ENIG, 1 oz outer / 0.5 oz inner copper. The controlled package contains all eight copper Gerbers, drills, IPC-D-356, BOM, placement, drawings, KiCad sources and the 76-site epoxy-fill/copper-cap POFV control. Current checks: ERC 0, DRC errors 0, unconnected 0. Three Altium `Net Antennae` warnings are accepted import-rule artifacts because route and physical-path parity is complete and the native KiCad board is clean.

PCB-PWR is 4-layer and PCB-MIC is 2-layer. Both have complete Gerber/drill/IPC-D-356/BOM/placement/STEP packages, DRC errors 0 and unconnected 0. Their active `STATUS.json` records are `ACCEPTED` for the EVT build.

The public factory/DFM basis is `hardware/reviews/EVT_FACTORY_PUBLIC_CAPABILITY_BASELINE_REV_B.json`. The strict release report is `artifacts/evt_pre_20_evt_build_release_audit_final.json` and is `PASS`.

The customer owns order placement. At checkout the customer must select the controlled stack/material options, require epoxy fill and copper cap for all 76 MAIN locations, resolve every upload-parser/DFM error without automatic geometry changes, download and compare the job-specific production files, and confirm them in the factory portal.

Physical first-article checks remain mandatory before the remaining lot or any serial transfer: SPI/AOI/X-ray, current-limited startup, PWR protection/thermal/cold/EMI, RF/antenna tests, MIC acoustic calibration, harness crimp/electrical checks and housing fit/seal/IP/service checks.

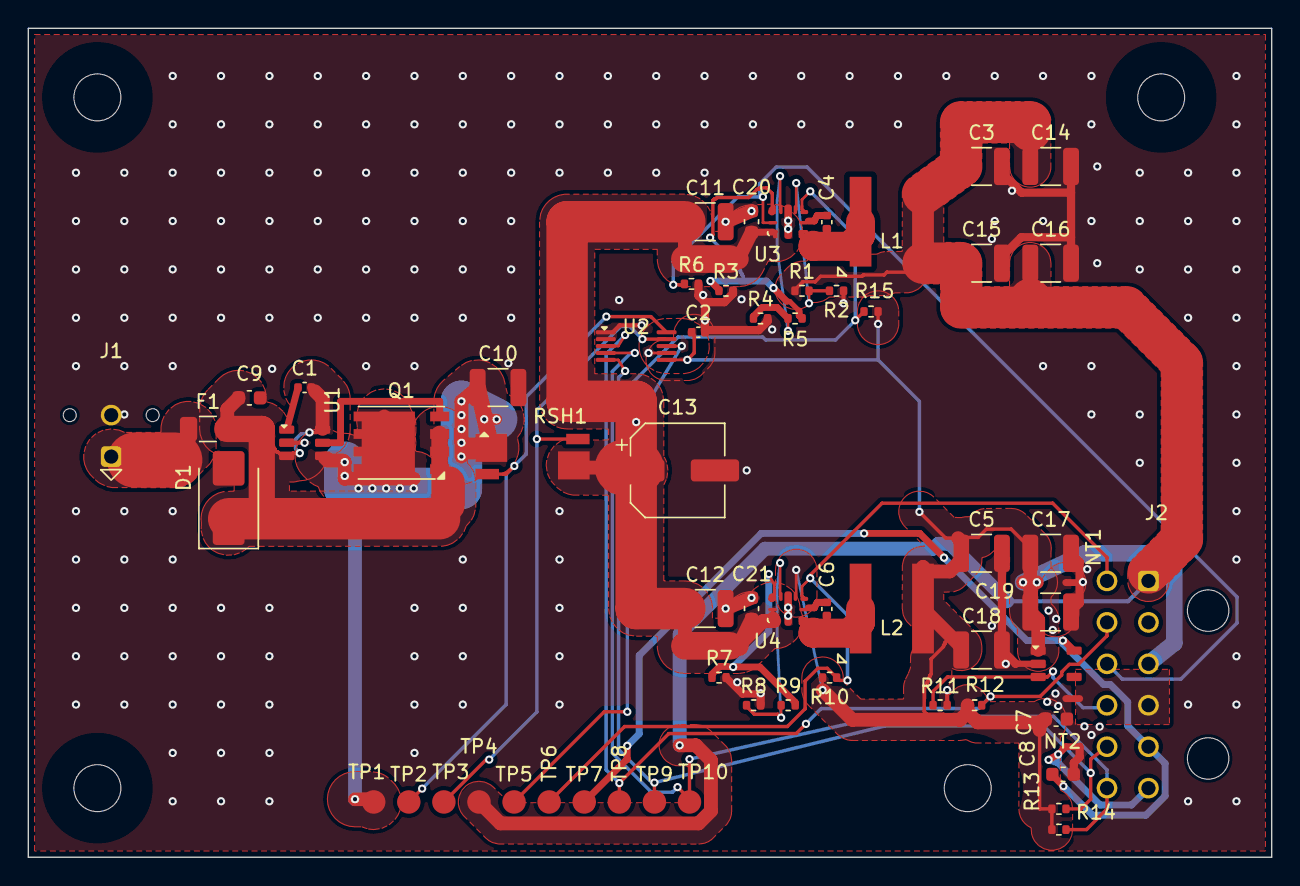
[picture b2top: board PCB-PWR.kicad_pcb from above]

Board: 4 copper layers, 90.0 x 60.0 mm, 66 parts (0 on the bottom side), 31 nets.

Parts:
C1, C2, C4, C6: 100 nF 25 V X7R CGA2B3X7R1E104K050BB; C_0402_1005Metric
C3, C5, C14, C15, C16, C17, C18, C19: 22 uF 25 V X7R CGA6P3X7R1E226M250AB; C_1210_3225Metric
C7, C8: 2.2 uF 10 V X7R CGA3E1X7R1A225K080AC; C_0603_1608Metric
C9, C20, C21: 100 nF 50 V X7R CGA3E2X7R1H104K080AA; C_0603_1608Metric
C10, C11, C12: 4.7 uF 50 V X7R CGA6P3X7R1H475K250AB; C_1210_3225Metric
C13: 100 uF 35 V hybrid EEH-ZK1V101XP; CP_Elec_6.3x7.7
D1: SMBJ18A CANDIDATE; D_SMB
F1: 0451008.MRL; Fuse_1206_3216Metric
H1, H2, H3, H4: M3_CLEARANCE_NPTH_3.4; MountingHole_M3_3.4_EVT
J1: 43045-0213; Molex_43045-0213_MicroFit-2_Vertical
J2: 43045-1202; Molex_43045-1202_MicroFit-12_RA
L1, L2: XAL7030-472MEC; Coilcraft_XAL7030_472
NT1, NT2, NT3: 2-pad copper net tie NET_TIE_COPPER_REV_A; NetTie-2_SMD_Pad0.5mm
Q1: CSD18540Q5B; CSD18540Q5B_DNK
R1: 100 kOhm 0.1% ERA-2AEB104X; R_0402_1005Metric
R2: 35.7 kOhm 0.1% ERA-2AEB3572X; R_0402_1005Metric
R3, R7: 86.6 kOhm 0.1% ERA-2AEB8662X; R_0402_1005Metric
R4, R5, R8, R9: 0 ohm ERJ-2GE0R00X; R_0402_1005Metric
R6, R11: 100 kOhm 1% ERJ-2RKF1003X; R_0402_1005Metric
R10, R12, R15: 10 kOhm 1% ERJ-2RKF1002X; R_0402_1005Metric
R13, R14: 4.7 kOhm 1% ERJ-2RKF4701X; R_0402_1005Metric
RSH1: WSK2512R0100FEA; Vishay_WSK2512_4T_T1.19mm
TP1: TP_VBAT_PROTECTED DFT_PAD_1P70_NOPASTE_REV_A; TestPoint_DFT_1.7mm_NoPaste
TP2: TP_SHUNT_SRC DFT_PAD_1P70_NOPASTE_REV_A; TestPoint_DFT_1.7mm_NoPaste
TP3: TP_SHUNT_LOAD DFT_PAD_1P70_NOPASTE_REV_A; TestPoint_DFT_1.7mm_NoPaste
TP4: TP_3V8 DFT_PAD_1P70_NOPASTE_REV_A; TestPoint_DFT_1.7mm_NoPaste
TP5: TP_PG_3V8 DFT_PAD_1P70_NOPASTE_REV_A; TestPoint_DFT_1.7mm_NoPaste
TP6: TP_PWR_GOOD DFT_PAD_1P70_NOPASTE_REV_A; TestPoint_DFT_1.7mm_NoPaste
TP7: TP_1V8 DFT_PAD_1P70_NOPASTE_REV_A; TestPoint_DFT_1.7mm_NoPaste
TP8: TP_FAULT DFT_PAD_1P70_NOPASTE_REV_A; TestPoint_DFT_1.7mm_NoPaste
TP9: TP_SCL DFT_PAD_1P70_NOPASTE_REV_A; TestPoint_DFT_1.7mm_NoPaste
TP10: TP_SDA DFT_PAD_1P70_NOPASTE_REV_A; TestPoint_DFT_1.7mm_NoPaste
U1: LM74700QDBVRQ1; TI_DBV0006A_SOT23-6
U2: INA226AIDGSR; TI_DGS0010A_VSSOP10
U3, U4: LMR604403SRAKR; LMR60440_RAK0009A
U5: TPS7A2018PDBVR; TI_DBV0005A_SOT23-5

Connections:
1V8_MIC: C8.1, J2.5, TP7.1, U5.5
3V3_DIGITAL: C2.1, C5.1, C7.1, C17.1, C18.1, C19.1, J2.3, L2.2, R10.1, R12.1, R13.1, R14.1, R15.2, U2.6, U4.6, U5.1
3V8_MODEM: C3.1, C14.1, C15.1, C16.1, J2.1, L1.2, R1.1, TP4.1
BOOT_3V3: C6.1, U4.4
BOOT_3V8: C4.1, U3.4
EN_AUX: J2.10, R11.1, U5.3
EN_MODEM: J2.9, R6.1, U3.9
FAULT: J2.8, R12.2, TP8.1, U2.3
FB_3V8: R1.2, R2.1, U3.6
GND_DIGITAL: J2.4, NT2.1
GND_MIC: J2.6, NT3.1
GND_MODEM: J2.2, NT1.1
GND_PWR: C2.2, C3.2, C5.2, C7.2, C8.2, C9.2, C10.2, C11.2, C12.2, C13.2, C14.2, C15.2, C16.2, C17.2, C18.2, C19.2, C20.2, C21.2, D1.2, J1.2, NT1.2, NT2.2, NT3.2, R2.2, R3.2, R4.2, R6.2, R7.2, R8.2, R11.2, U1.2, U2.1, U2.2, U2.7, U3.2, U4.2, U5.2
I2C2_SCL: J2.11, R13.2, TP9.1, U2.5
I2C2_SDA: J2.12, R14.2, TP10.1, U2.4
LM74700_VCAP: C1.1, U1.1
MODE_3V3: R8.1, R9.1, U4.7
MODE_3V8: R4.1, R5.1, U3.7
PG_3V8: R15.1, TP5.1, U3.5
PWR_GOOD: J2.7, R10.2, TP6.1, U4.5
REV_GATE: Q1.4, U1.5
RT_3V3: R7.1, R9.2, U4.8
RT_3V8: R3.1, R5.2, U3.8
SHUNT_LOAD_SENSE: RSH1.4, TP3.1, U2.9
SHUNT_SOURCE_SENSE: RSH1.3, TP2.1, U2.10
SW_3V3: C6.2, L2.1, U4.3
SW_3V8: C4.2, L1.1, U3.3
VBAT_FUSED: C1.2, C9.1, D1.1, F1.2, Q1.1, Q1.2, Q1.3, U1.3, U1.6
VBAT_PROTECTED: C10.1, Q1.5, Q1.6, Q1.7, Q1.8, RSH1.1, TP1.1, U1.4
VBAT_RAW: F1.1, J1.1
VBAT_SYS: C11.1, C12.1, C13.1, C20.1, C21.1, RSH1.2, U2.8, U3.1, U4.1, U4.9

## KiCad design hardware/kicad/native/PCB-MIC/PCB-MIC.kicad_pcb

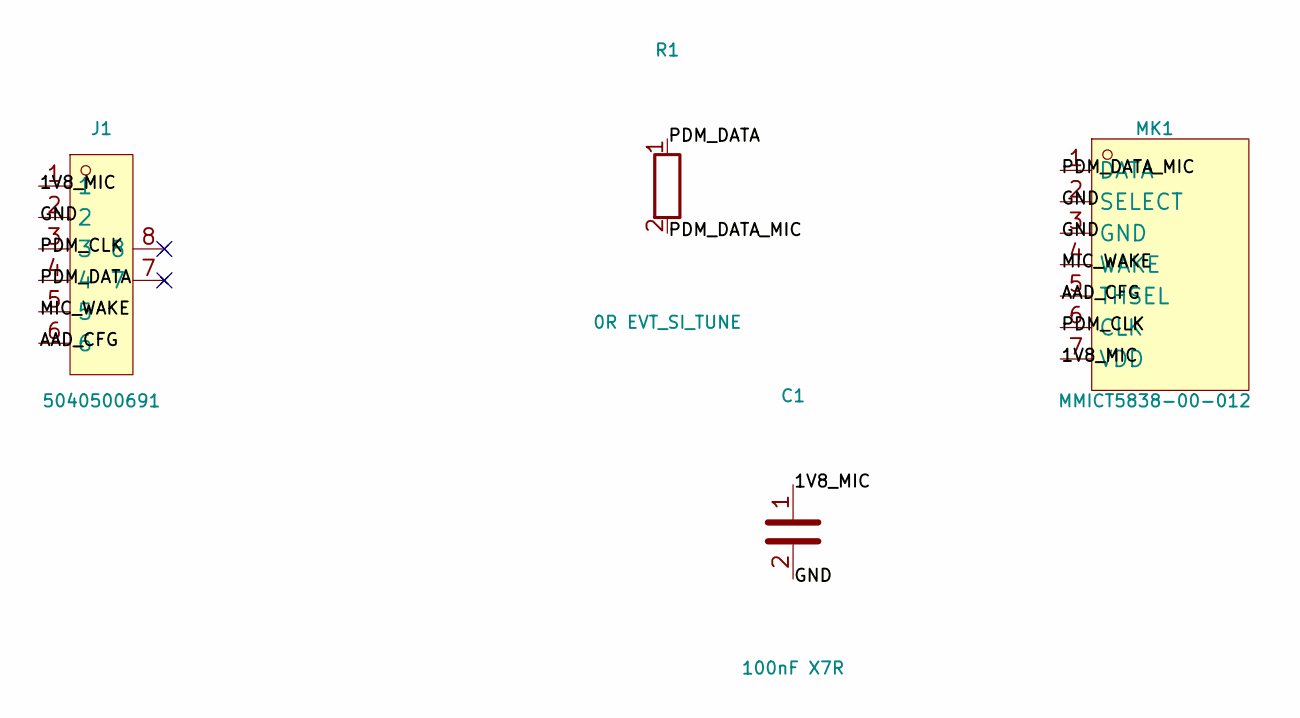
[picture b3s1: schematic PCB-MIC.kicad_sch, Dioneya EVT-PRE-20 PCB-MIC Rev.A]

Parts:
C1: 100nF X7R; C_0402_1005Metric
J1: 5040500691; Molex_5040500691
MK1: MMICT5838-00-012; T5838_RevA
R1: 0R EVT_SI_TUNE; R_0402_1005Metric

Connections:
/1V8_MIC: C1.1, J1.1, MK1.7 (VDD)
/AAD_CFG: J1.6, MK1.5 (THSEL)
/GND: C1.2, J1.2, MK1.2 (SELECT), MK1.3 (GND)
/MIC_WAKE: J1.5, MK1.4 (WAKE)
/PDM_CLK: J1.3, MK1.6 (CLK)
/PDM_DATA: J1.4, R1.1
/PDM_DATA_MIC: MK1.1 (DATA), R1.2

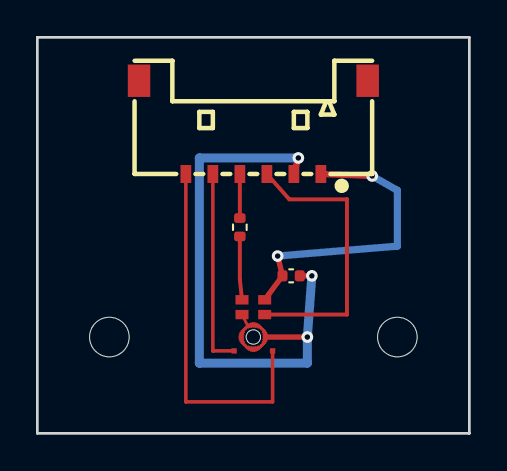
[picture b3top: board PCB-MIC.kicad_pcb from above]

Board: 2 copper layers, 24.0 x 22.0 mm, 6 parts (0 on the bottom side), 7 nets.

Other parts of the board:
H1, H2: M2_CLEARANCE_NPTH_2.2
